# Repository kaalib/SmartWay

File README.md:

#Smartway
Video Summary: [Smartway](https://youtu.be/klQwbzWfP6Y?si=fyRBp5o61DdSwOSP)

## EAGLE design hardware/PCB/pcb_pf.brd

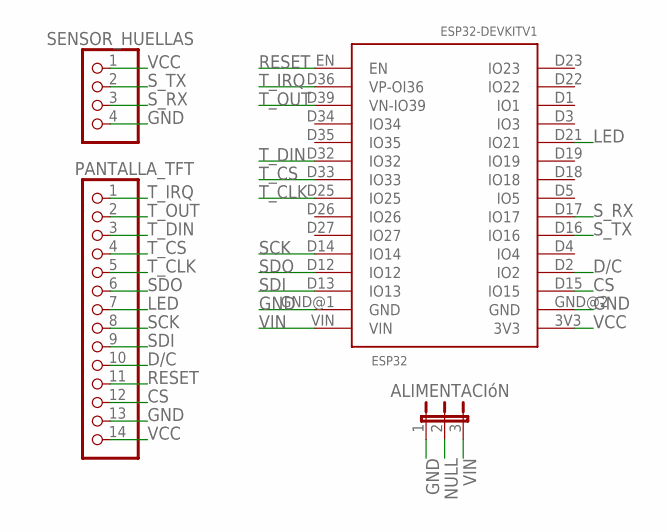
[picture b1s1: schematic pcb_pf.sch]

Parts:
ALIMENTACIóN: JP2E; JP2
ESP32: ESP32DEVKITV1; ESP32-DEVKITV1
PANTALLA_TFT: PINHD-1X14; 1X14
SENSOR_HUELLAS: PINHD-1X4; 1X04

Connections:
CS: ESP32.D15 (IO15), PANTALLA_TFT.12
D/C: ESP32.D2 (IO2), PANTALLA_TFT.10
GND: ALIMENTACIóN.1, ESP32.GND@1 (GND), ESP32.GND@2 (GND), PANTALLA_TFT.13, SENSOR_HUELLAS.4
LED: ESP32.D21 (IO21), PANTALLA_TFT.7
NULL: ALIMENTACIóN.2
RESET: ESP32.EN, PANTALLA_TFT.11
SCK: ESP32.D14 (IO14), PANTALLA_TFT.8
SDI: ESP32.D13 (IO13), PANTALLA_TFT.9
SDO: ESP32.D12 (IO12), PANTALLA_TFT.6
S_RX: ESP32.D17 (IO17), SENSOR_HUELLAS.3
S_TX: ESP32.D16 (IO16), SENSOR_HUELLAS.2
T_CLK: ESP32.D25 (IO25), PANTALLA_TFT.5
T_CS: ESP32.D33 (IO33), PANTALLA_TFT.4
T_DIN: ESP32.D32 (IO32), PANTALLA_TFT.3
T_IRQ: ESP32.D36 (VP-OI36), PANTALLA_TFT.1
T_OUT: ESP32.D39 (VN-IO39), PANTALLA_TFT.2
VCC: ESP32.3V3, PANTALLA_TFT.14, SENSOR_HUELLAS.1
VIN: ALIMENTACIóN.3, ESP32.VIN

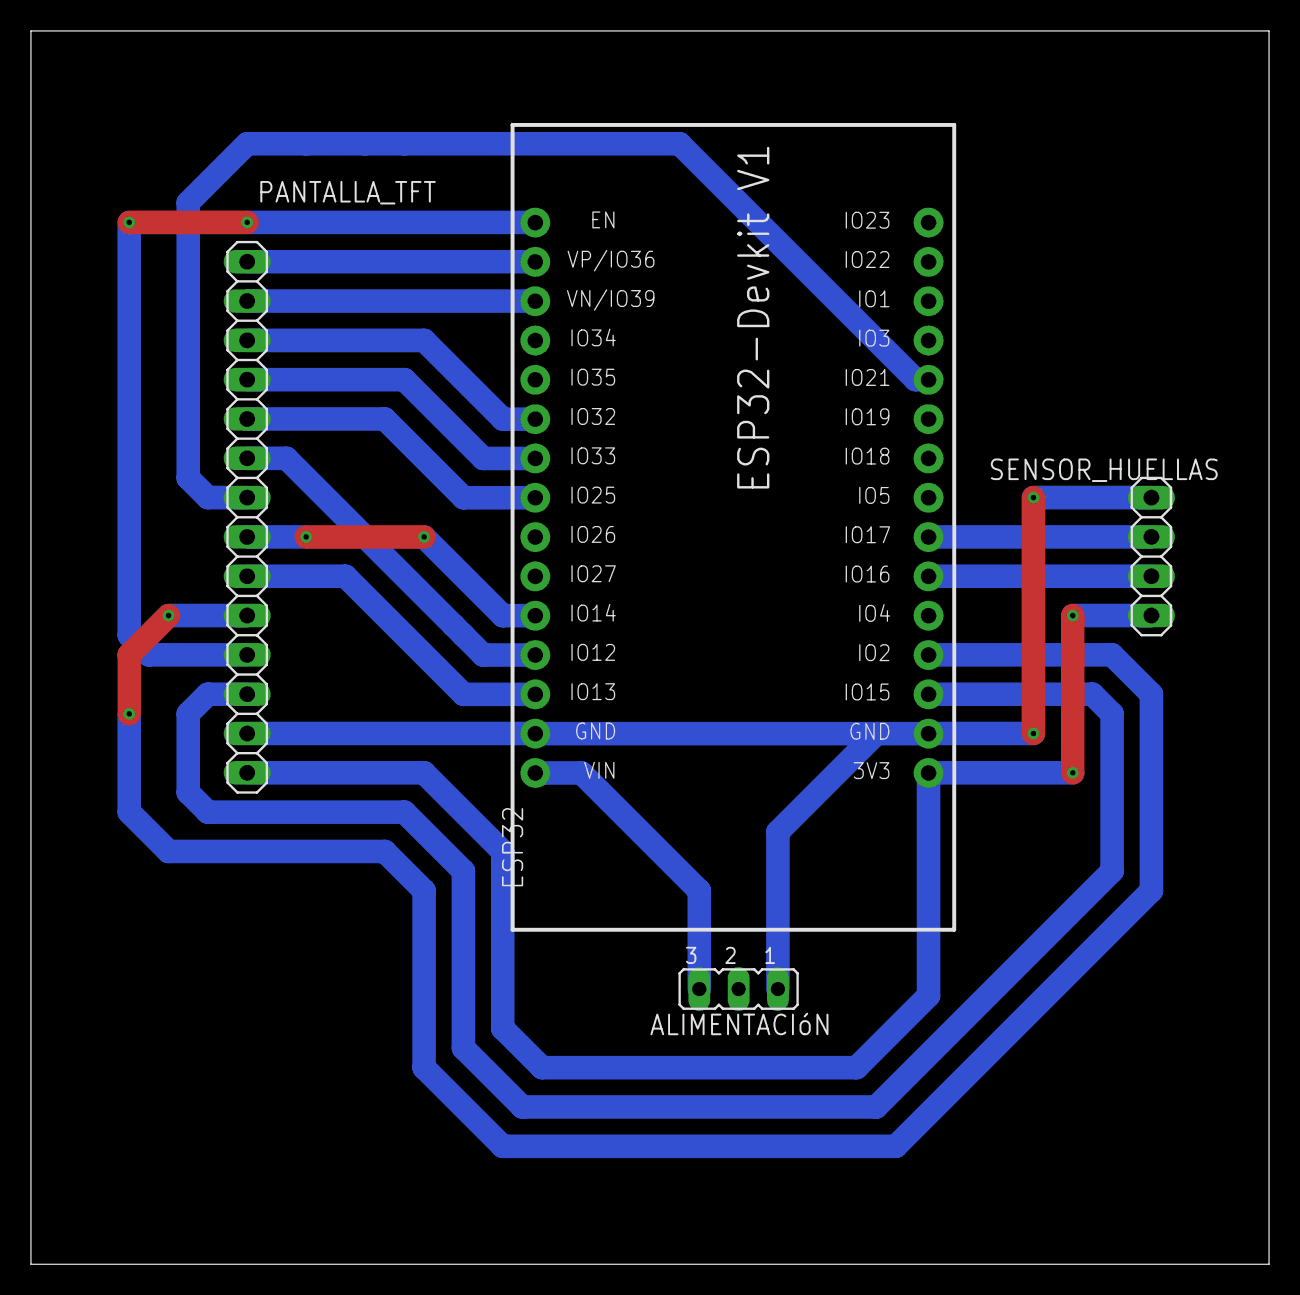
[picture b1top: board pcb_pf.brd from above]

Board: 2 copper layers, 80.0 x 79.7 mm, 4 parts (0 on the bottom side), 17 nets.

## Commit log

2025-02-01 new b
2025-02-01 new index.html
2025-02-01 test putty
2025-02-03 create server.js v2
2025-02-03 create server.js v3
2025-02-03 create server.js v4
2025-02-03 create server.js v5
2025-02-05 create css and improve server
2025-02-07 test ci/cd
2025-02-07 test btn and map_tom
2025-02-07 fix server.js v1
2025-02-07 fix server.js v2
2025-02-07 fix server.js v3
2025-02-07 fix server.js v4
2025-02-07 fix server.js v5
2025-02-07 test https
2025-02-07 test https and map
2025-02-07 test https and map v2
2025-02-07 test https and map v3
2025-02-07 add dependecies and modules
2025-02-07 fix server.js
2025-02-08 fix links
2025-02-08 fix links v2
2025-02-08 fix map
2025-02-08 fix map v3
2025-02-08 fix map v4
2025-02-11 fix index.html
2025-02-11 fix index.html v2
2025-02-11 fix index.html v3
2025-02-11 fix index.html v4
2025-02-11 fix index.html v5
2025-02-11 fix index.html v6
2025-02-12 test mysql connection
2025-02-12 test mysql connection v2
2025-02-12 test get address from mysql
2025-02-13 Códigos de registro y envío de huellas al servidor
2025-02-14 test push directions in map
2025-02-14 test push direction on map
2025-02-14 test push direction on map v2
2025-02-14 test push direction on map v3
2025-02-14 test push direction on map v5
2025-02-14 test push direction on map v6
2025-02-14 test push direction on map v7
2025-02-15 test push direction on map v8
2025-02-15 test push direction on map v9
2025-02-15 test push direction on map v10
2025-02-15 test push direction on map v11
2025-02-18 change frontend
2025-02-18 change frontend v2
2025-02-19 change frontend v3
2025-02-19 change frontend v4
2025-02-19 Código GUI incluida lógica de botones enroll y fingerprint
2025-02-21 test login
2025-02-21 test login v2
2025-02-21 test location v1
2025-02-21 improve frontend
2025-02-21 improve frontend v2
2025-02-21 Cambio de version de la libreria LGVL de 9 a 8.3.11 y mensaje inicial
2025-02-22 improve frontend v3
2025-02-22 improve frontend v4
2025-02-22 improve frontend v5
2025-02-22 improve frontend v6
2025-02-22 Botones funcionales y colores correctos
2025-02-22 test googleapi
2025-02-22 test googleapi v2
2025-02-22 include sweetalert and test map
2025-02-22 include sweetalert and test map v2
2025-02-23 try fix map
2025-02-23 try fix map v2
2025-02-24 try fix map v3
2025-02-24 improve map visualization
2025-02-24 test drawmarkers button
2025-02-24 test drawmarkers button v2
2025-02-25 improve mobile ui
2025-02-25 improve mobile ui v2
2025-02-25 improve mobile ui v3
2025-02-27 Botón fingerprint con simulacion del sensor conectado
2025-02-27 dos botones y boton fingerprint con logica real incluida
2025-03-01 test login with users and improve fetch data
2025-03-02 Solo botón fingerprint leyendo huellas
2025-03-02 Botón con lector de huellas, esp32 con wifi y envío TCP, UDP
2025-03-02 Eliminando archivos sensibles del historial
2025-03-02 Eliminando archivos sensibles del historial.2
2025-03-06 test coneection to api
2025-03-07 test http api request
2025-03-08 test api and add icons
2025-03-08 test ci/cd with ython
2025-03-09 test directionbus
2025-03-09 test directionbus v2 + busmarker
2025-03-10 test directionbus v3
2025-03-10 test directionbus v4
2025-03-11 test websocket y sendubi10segs
2025-03-11 test websocket y sendubi10segs v2
2025-03-11 test websocket y sendubi10segs v3
2025-03-11 test websocket y sendubi10segs v4
2025-03-11 test websocket y sendubi10segs v5
2025-03-11 test websocket y sendubi10segs v6
2025-03-12 test websocket in 3roles
2025-03-12 test websocket in 3roles fix app.post
2025-03-12 test 3pages
2025-03-13 test drawmarkers10segs
2025-03-13 test drawmarkers10segs v2
2025-03-13 test drawmarkers10segs v3
2025-03-13 test drawmarkers10segs v4
2025-03-13 test drawmarkers10segs v5
2025-03-13 test drawmarkers10segs v6
2025-03-13 test drawmarkers10segs v7
2025-03-13 test drawmarkers10segs v8
2025-03-13 test drawmarkers10segs v9
2025-03-20 test ubibus
2025-03-20 test ubibus v2
2025-03-20 test ubibus v3
2025-03-20 test ubibus v4
2025-03-20 test ubibus v5
2025-03-20 test ubibus v6
2025-03-20 test ubibus v7
2025-03-20 GA of distance hiding the API key with environment variables
2025-03-20 GA with distance and traffic
2025-03-25 folder fixed GA
2025-03-25 code for routes with distance and traffic
2025-03-25 test IA v2
2025-03-25 test IA v3
2025-03-25 test IA v4
2025-03-25 test IA v5
2025-03-25 test IA v6
2025-03-25 test IA v7
2025-04-05 improve frontend and test map.js
2025-04-05 fix map.js v2
2025-04-06 improve map frontend
2025-04-06 version before microservices
2025-04-06 test microservicios in cloud
2025-04-06 test microservicios in cloud v2
2025-04-06 test microservicios in cloud v3
2025-04-06 test microservicios in cloud v4
2025-04-06 test microservicios in cloud v10
2025-04-06 test microS and mapID
2025-04-06 test microS and mapID v2
2025-04-06 test microS and mapID v3
2025-04-07 test navigation and sockets
2025-04-07 test sockets and tcp messages
2025-04-07 test sockets and tcp messages main correction
2025-04-08 test busmarker and new array []
2025-04-08 test busmarker and new array [] v2
2025-04-08 test busmarker and new array [] v3 fix ubicación bus
2025-04-08 test busmarker and new array [] v3 fix ubicación bus v2
2025-04-08 test busmarker and new array [] v3 fix ubicación bus v3
2025-04-08 test busmarker and new array [] v3 fix ubicación bus v3 and fic flask v1
2025-04-08 test busmarker and new array [] v3 fix ubicación bus v3 and fic flask v2
2025-04-08 test busmarker and new array [] v3 fix ubicación bus v3 and fic flask v3
2025-04-08 test busmarker and new array [] v3 fix ubicación bus v3 and fic flask v4
2025-04-08 test busmarker and new array [] v3 fix ubicación bus v3 and fic flask v5
2025-04-08 test busmarker and new array [] v3 fix ubicación bus v3 and fic flask v6
2025-04-08 test busmarker and limit tcpconnections
2025-04-08 test busmarker and limit tcpconnections v2
2025-04-08 test busmarker and limit tcpconnections v3
2025-04-09 test busmarker and limit tcpconnections v4
2025-04-09 test all
2025-04-09 test all v2
2025-04-09 test all v3
2025-04-09 test map and create fronted
2025-04-09 test map again
2025-04-09 test server
2025-04-09 test server v3
2025-04-09 test server v4
2025-04-09 test server v4 and web clients
2025-04-11 test beta1
2025-04-11 test beta2
2025-04-11 test beta2.1
2025-04-12 test beta2.2
2025-04-12 test beta2.3
2025-04-12 test beta2.4
2025-04-12 test beta2.5
2025-04-12 test beta2.51
2025-04-12 test beta2.52
2025-04-12 test beta2.53
2025-04-13 test beta3
2025-04-13 test beta3.1
2025-04-13 test beta4
2025-04-13 test beta4.1
2025-04-13 test beta5
2025-04-13 restart pf to earlier version
2025-04-13 restart pf to earlier version in orla branch
2025-04-13 test commit
2025-04-13 test change server.js and locations.js
2025-04-13 add .env ubuntu
2025-04-15 test beta 6
2025-04-15 test beta 6.1
2025-04-15 test beta 6.2
2025-04-16 test beta 6.3
2025-04-16 test beta 6.4
2025-04-16 test beta 6.5
2025-04-16 test beta 6.6
2025-04-16 test beta 6.7
2025-04-17 test beta 6.8
2025-04-17 new screen interface
2025-04-17 Interface complete
2025-04-28 add python to historical data
2025-04-28 fix .env
2025-04-28 fix .env and create logfile
2025-04-28 historical_data ajusted for the free trier APIs
2025-04-28 fix .env karenversion
2025-04-28 fix .env karenversion test 2
2025-04-28 fix .env karenversion test 3
2025-04-29 fix .env karenversion test 4
2025-04-29 fix .env karenversion test 5
2025-04-30 buttons, UX in ili9341 and tomtom accidents URL changes
2025-05-02 IA algorithm with the neuronal network and stadistics files
2025-05-04 real addresses
2025-05-04 real addresses and 101 pairs
2025-05-04 addresses de historical_Data
2025-05-04 final addresses
2025-05-05 direccion corregida en soledad
2025-05-05 rutas optimizadas con direcciones reales de barranquilla
2025-05-06 no tomtom api request
2025-05-06 only 50 pairs per execution
2025-05-08 traffic level using tomtom
2025-05-08 new model
2025-05-13 loading a neural model with 0.8 accuracy and main script with a TSP
2025-05-13 70 pairs per hour
2025-05-13 debbuging
2025-05-13 INFO
2025-05-13 add team and try navigation.js
2025-05-14 add pcb and improve navigation and ui
2025-05-14 add historical data for admis
2025-05-14 add historical data for admis fix config
2025-05-14 Improve in GA, IA and hardware interface
2025-05-14 test historial page v2
2025-05-14 test historial page v3
2025-05-14 test historial page v4
2025-05-14 test historial page v5
2025-05-14 test historial page v6
2025-05-14 upload flask with neural network
2025-05-15 test ci/cd v2
2025-05-17 fix location permission and improve frontend
2025-05-17 fix flask and permissions
2025-05-17 fix flask v3
2025-05-17 fix flask v4
2025-05-17 fix flask v5
2025-05-17 fix flask v6
2025-05-17 fix flask v7
2025-05-18 change dotenv historical data
2025-05-20 improve hardware id if the battery is low and 30 pais of addresses in the cron
2025-05-26 add pf consultor advise
2025-05-26 add u2 video
